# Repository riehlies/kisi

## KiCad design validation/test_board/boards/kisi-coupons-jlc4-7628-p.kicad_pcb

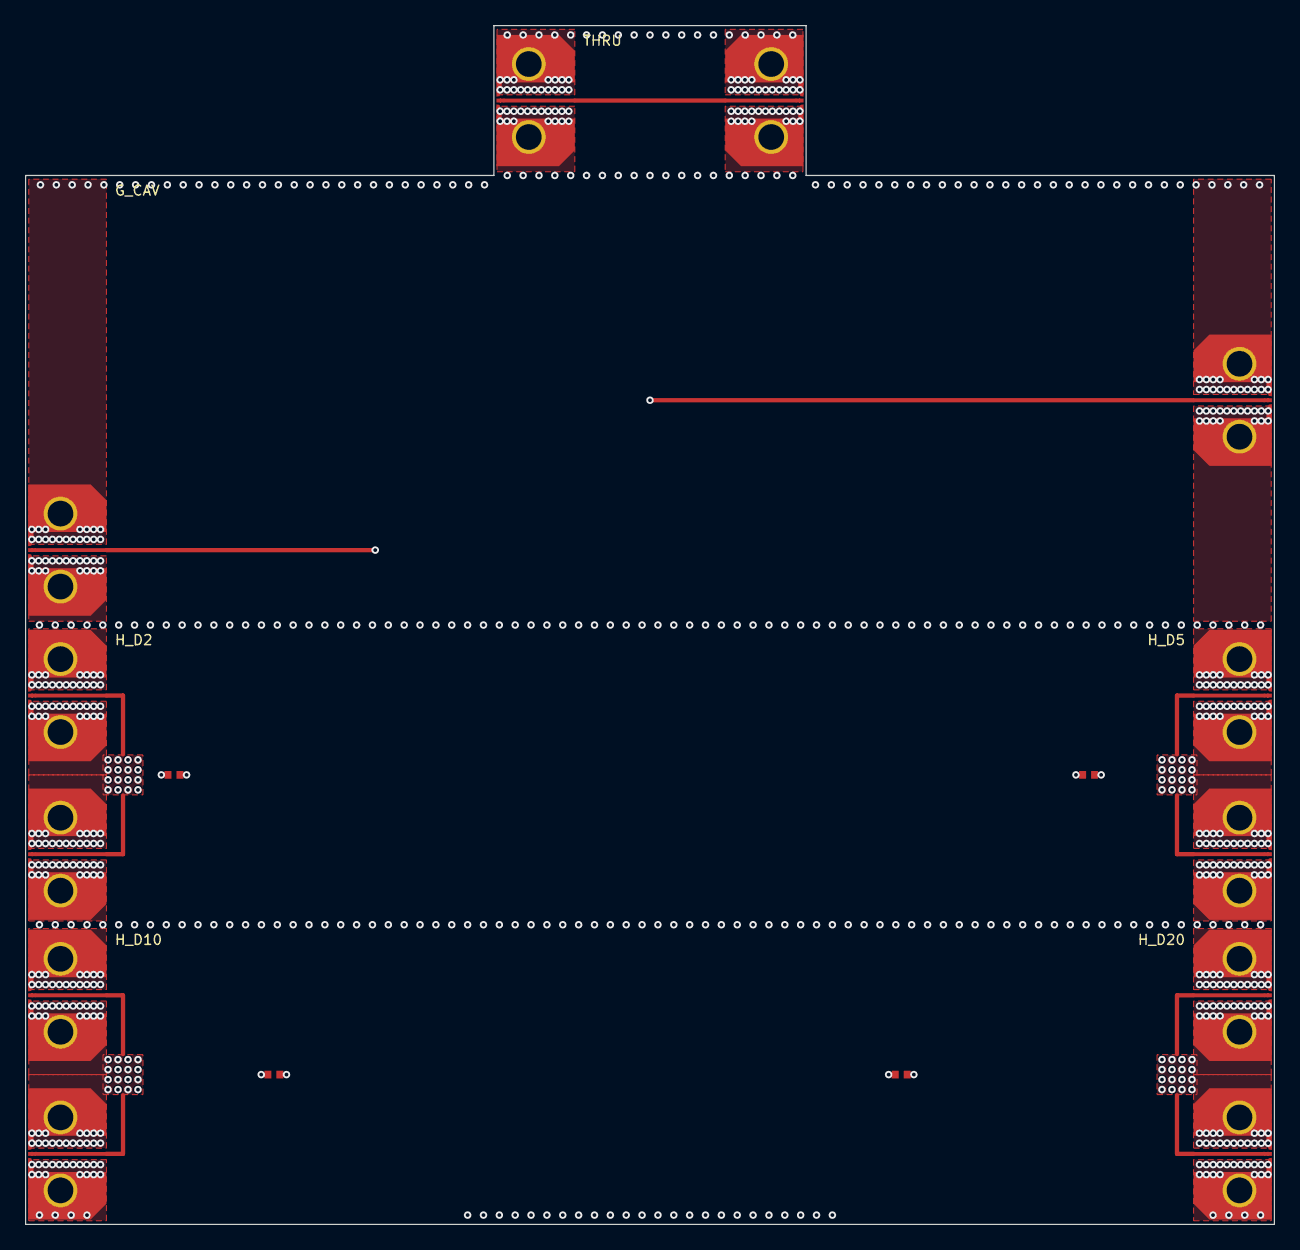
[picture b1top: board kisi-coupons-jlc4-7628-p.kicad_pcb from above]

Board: 4 copper layers, 100.0 x 96.0 mm, 20 parts (0 on the bottom side), 7 nets.

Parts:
C1, C2, C3, C4: 100nF 16V X7R; C_0402_1005Metric
J1, J2, J3, J4, J5, J6, J7, J8, J9, J10, J11, J12: 292-J-P-EP-ST-EL-01; Samtec_292-J-P-EP-ST-EL-01_EdgeLaunch_W0.315
U1: pin field (no part); U_VDD_H_D2
U2: pin field (no part); U_VDD_H_D5
U3: pin field (no part); U_VDD_H_D10
U4: pin field (no part); U_VDD_H_D20

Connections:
CAV_G_CAV: J3.1, J4.1
GND: C1.1, C2.2, C3.1, C4.2, J1.2, J1.3, J2.2, J2.3, J3.2, J3.3, J4.2, J4.3, J5.2, J5.3, J6.2, J6.3, J7.2, J7.3, J8.2, J8.3, J9.2, J9.3, J10.2, J10.3, J11.2, J11.3, J12.2, J12.3, U1.A2, U1.A4, U1.B1, U1.B3, U1.C2, U1.C4, U1.D1, U1.D3, U2.A2, U2.A4, U2.B1, U2.B3, U2.C2, U2.C4, U2.D1, U2.D3, U3.A2, U3.A4, U3.B1, U3.B3, U3.C2, U3.C4, U3.D1, U3.D3, U4.A2, U4.A4, U4.B1, U4.B3, U4.C2, U4.C4, U4.D1, U4.D3
SE_THRU: J1.1, J2.1
VDD_H_D2: C1.2, J5.1, J6.1, U1.A1, U1.A3, U1.B2, U1.B4, U1.C1, U1.C3, U1.D2, U1.D4
VDD_H_D5: C2.1, J7.1, J8.1, U2.A1, U2.A3, U2.B2, U2.B4, U2.C1, U2.C3, U2.D2, U2.D4
VDD_H_D10: C3.2, J9.1, J10.1, U3.A1, U3.A3, U3.B2, U3.B4, U3.C1, U3.C3, U3.D2, U3.D4
VDD_H_D20: C4.1, J11.1, J12.1, U4.A1, U4.A3, U4.B2, U4.B4, U4.C1, U4.C3, U4.D2, U4.D4

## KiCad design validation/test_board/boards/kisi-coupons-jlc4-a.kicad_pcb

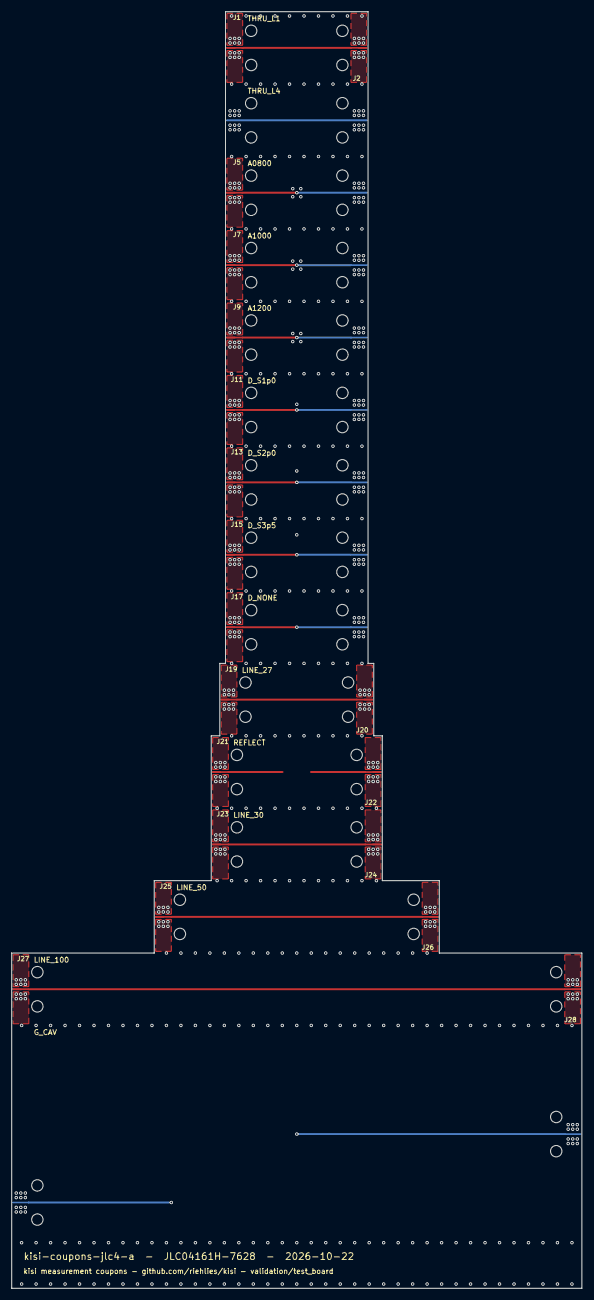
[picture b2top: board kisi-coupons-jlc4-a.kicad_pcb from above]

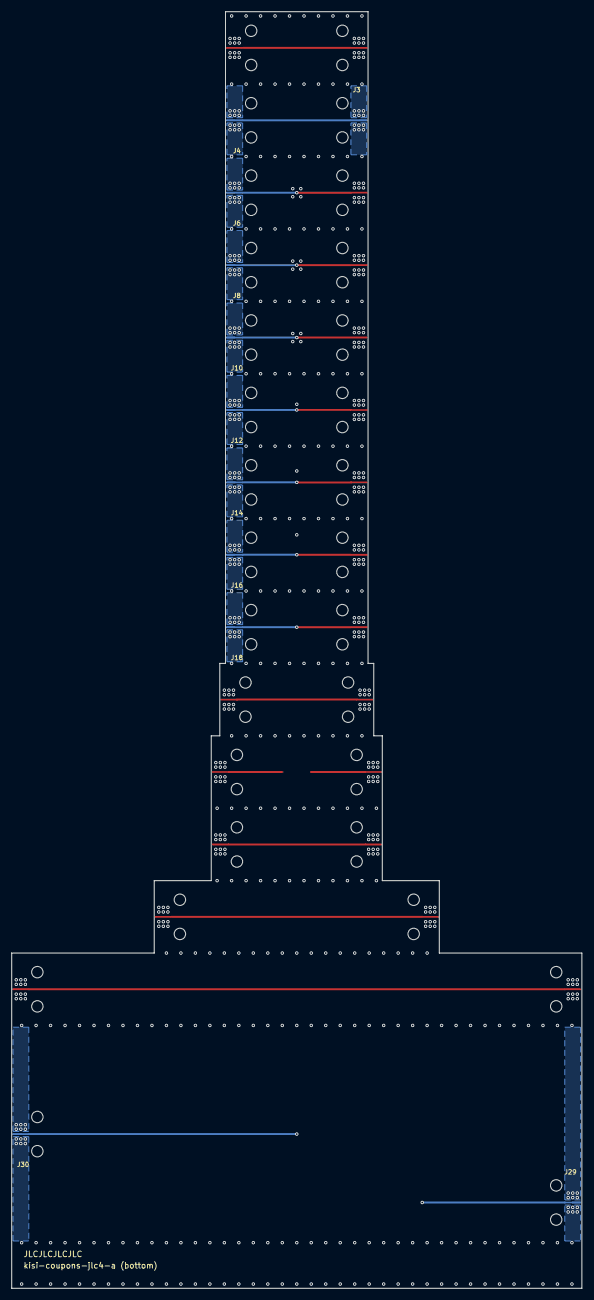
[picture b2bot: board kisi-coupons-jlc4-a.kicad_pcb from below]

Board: 4 copper layers, 100.0 x 223.9 mm, 30 parts (11 on the bottom side), 14 nets.

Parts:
J1, J2, J3, J4, J5, J6, J7, J8, J9, J10, J11, J12, J13, J14, J15, J16, J17, J18, J19, J20, J21, J22, J23, J24, J25, J26, J27, J28, J29, J30: 292-04A-14 / 1092-01A-14; SWM_EndLaunch_Narrow_PLACEHOLDER

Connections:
CAV: J29.1, J30.1
SE_A0800: J5.1, J6.1
SE_A1000: J7.1, J8.1
SE_A1200: J9.1, J10.1
SE_D_NONE: J17.1, J18.1
SE_D_S1p0: J11.1, J12.1
SE_D_S2p0: J13.1, J14.1
SE_D_S3p5: J15.1, J16.1
SE_LINE_27: J19.1, J20.1
SE_LINE_30: J23.1, J24.1
SE_LINE_50: J25.1, J26.1
SE_LINE_100: J27.1, J28.1
SE_THRU_L1: J1.1, J2.1
SE_THRU_L4: J3.1, J4.1

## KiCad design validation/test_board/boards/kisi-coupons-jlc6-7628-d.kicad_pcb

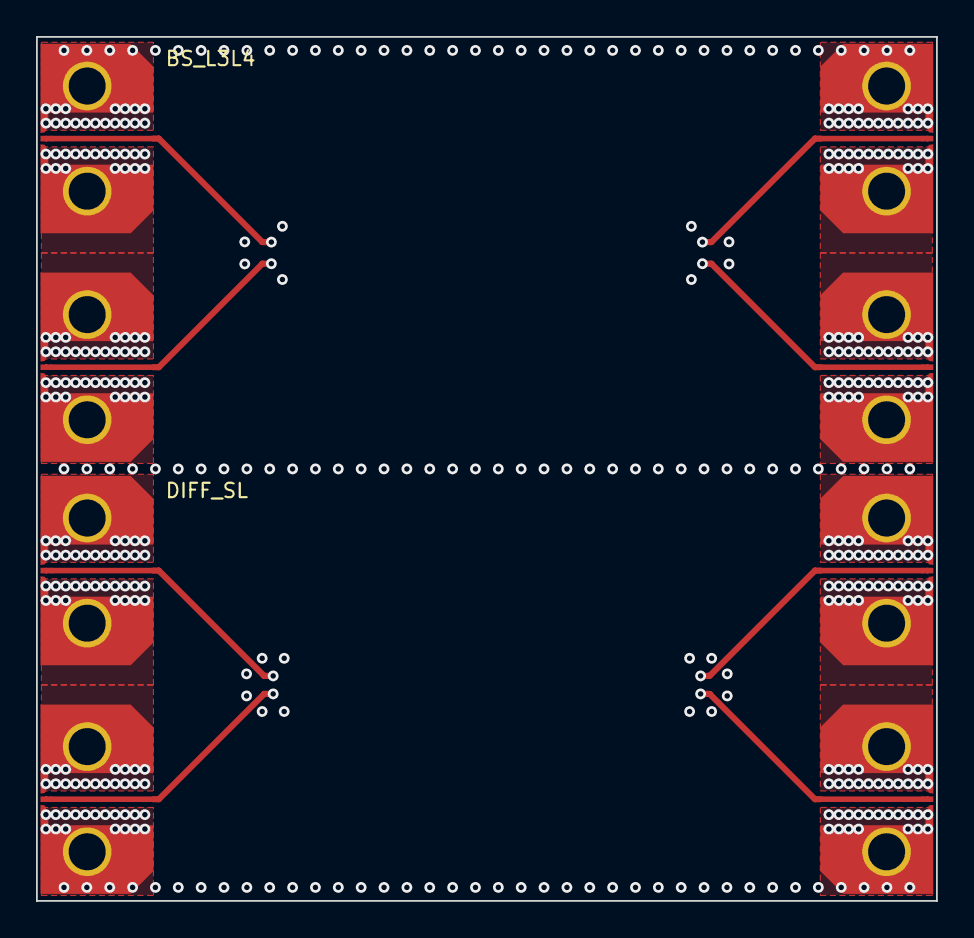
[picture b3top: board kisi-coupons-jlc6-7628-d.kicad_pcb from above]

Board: 6 copper layers, 50.0 x 48.0 mm, 8 parts (0 on the bottom side), 5 nets.

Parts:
J1, J2, J3, J4, J5, J6, J7, J8: 292-J-P-EP-ST-EL-01; Samtec_292-J-P-EP-ST-EL-01_EdgeLaunch_W0.315

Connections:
DP_DIFF_SL_N: J6.1, J8.1
DP_DIFF_SL_P: J5.1, J7.1
GND: J1.2, J1.3, J2.2, J2.3, J3.2, J3.3, J4.2, J4.3, J5.2, J5.3, J6.2, J6.3, J7.2, J7.3, J8.2, J8.3
SE_BS_A: J1.1, J3.1
SE_BS_V: J2.1, J4.1
